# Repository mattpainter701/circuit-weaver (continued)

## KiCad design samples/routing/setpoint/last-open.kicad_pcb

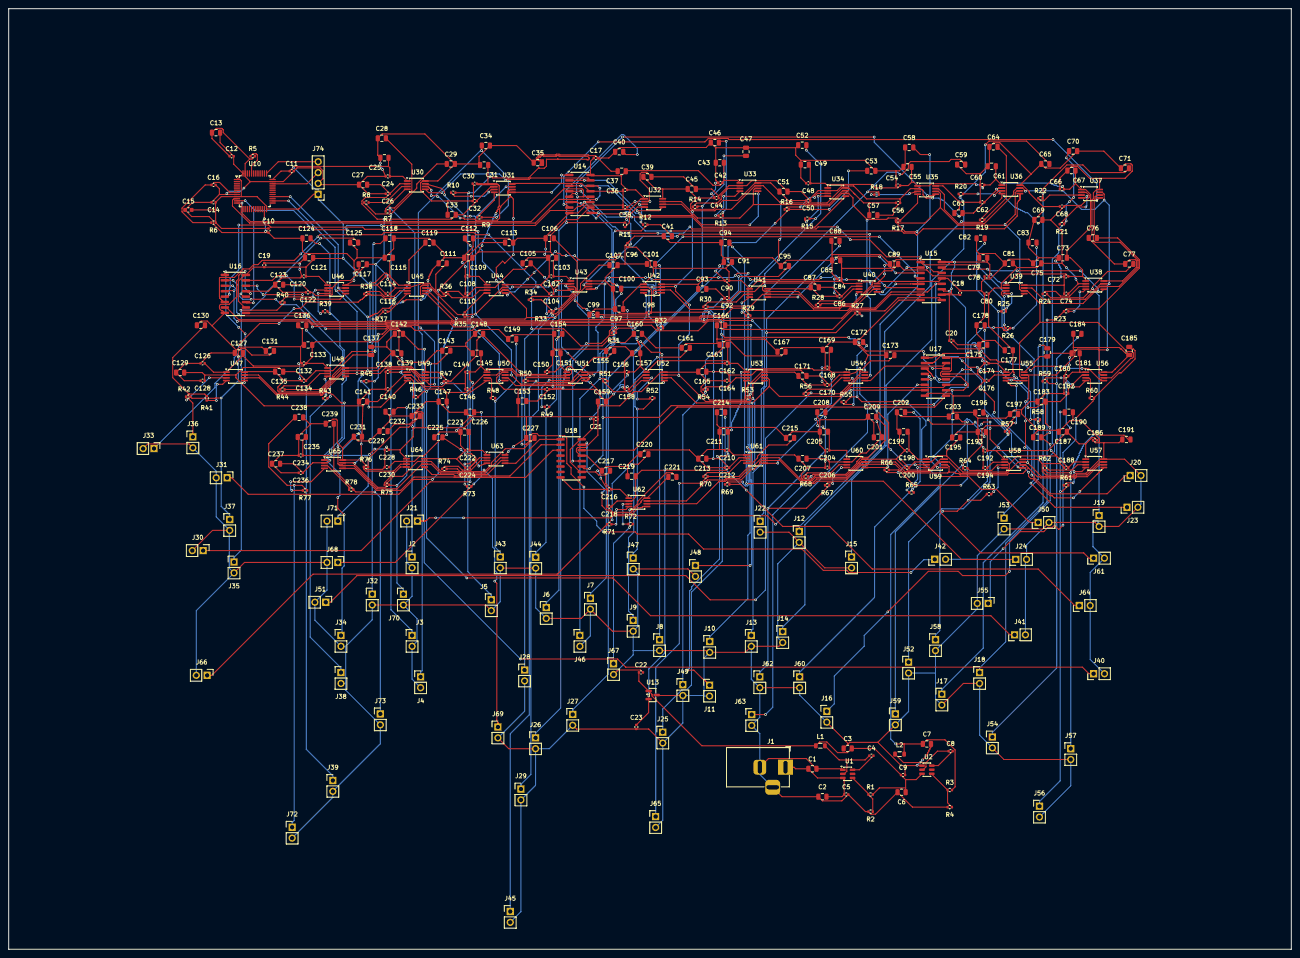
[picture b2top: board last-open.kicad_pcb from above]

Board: 2 copper layers, 300.0 x 220.0 mm, 438 parts (0 on the bottom side), 204 nets.

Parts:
C1, C2, C6, C25, C27, C31, C33, C37, C39, C43, C45, C49, C51, C55, C57, C61, C63, C67, C69, C73, C75, C79, C81, C85, C87, C91, C93, C97, C99, C103, C105, C109, C111, C115, C117, C121, C123, C127, C129, C133, C135, C139, C141, C145, C147, C151, C153, C157, C159, C163, C165, C169, C171, C175, C177, C181, C183, C187, C189, C193, C195, C199, C201, C205, C207, C211, C213, C217, C219, C223, C225, C229, C231, C235, C237: 10uF; C_0805_2012Metric
C3: 6.2uF; C_0805_2012Metric
C4, C5, C8, C9, C10, C11, C12, C16, C17, C18, C19, C20, C21, C22, C23, C24, C26, C30, C32, C36, C38, C42, C44, C48, C50, C54, C56, C60, C62, C66, C68, C72, C74, C78, C80, C84, C86, C90, C92, C96, C98, C102, C104, C108, C110, C114, C116, C120, C122, C126, C128, C132, C134, C138, C140, C144, C146, C150, C152, C156, C158, C162, C164, C168, C170, C174, C176, C180, C182, C186, C188, C192, C194, C198, C200, C204, C206, C210, C212, C216, C218, C222, C224, C228, C230, C234, C236: 100nF; C_0402_1005Metric
C7: 3.3uF; C_0805_2012Metric
C13: 4.7uF; C_0805_2012Metric
C14: 10nF; C_0402_1005Metric
C15: 1uF; C_0603_1608Metric
C28, C29, C34, C35, C40, C41, C46, C47, C52, C53, C58, C59, C64, C65, C70, C71, C76, C77, C82, C83, C88, C89, C94, C95, C100, C101, C106, C107, C112, C113, C118, C119, C124, C125, C130, C131, C136, C137, C142, C143, C148, C149, C154, C155, C160, C161, C166, C167, C172, C173, C178, C179, C184, C185, C190, C191, C196, C197, C202, C203, C208, C209, C214, C215, C220, C221, C226, C227, C232, C233, C238, C239: 1.5uF; C_0805_2012Metric
J1: BARREL_JACK_2.1MM; BarrelJack_Horizontal
J2, J3, J4, J5, J6, J7, J8, J9, J10, J11, J12, J13, J14, J15, J16, J17, J18, J19, J20, J21, J22, J23, J24, J25, J26, J27, J28, J29, J30, J31, J32, J33, J34, J35, J36, J37, J38, J39, J40, J41, J42, J43, J44, J45, J46, J47, J48, J49, J50, J51, J52, J53, J54, J55, J56, J57, J58, J59, J60, J61, J62, J63, J64, J65, J66, J67, J68, J69, J70, J71, J72, J73: PIN_HEADER_2P; PinHeader_1x02_P2.54mm_Vertical
J74: PIN_HEADER_4P; PinHeader_1x04_P2.54mm_Vertical
L1: 8.2uH; L_0805_2012Metric
L2: 6.2uH; L_0805_2012Metric
R1: 1.05M; R_0402_1005Metric
R2: 200k; R_0402_1005Metric
R3: 357k; R_0402_1005Metric
R4: 115k; R_0402_1005Metric
R5, R6: 10k; R_0402_1005Metric
R7, R8, R9, R10, R11, R12, R13, R14, R15, R16, R17, R18, R19, R20, R21, R22, R23, R24, R25, R26, R27, R28, R29, R30, R31, R32, R33, R34, R35, R36, R37, R38, R39, R40, R41, R42, R43, R44, R45, R46, R47, R48, R49, R50, R51, R52, R53, R54, R55, R56, R57, R58, R59, R60, R61, R62, R63, R64, R65, R66, R67, R68, R69, R70, R71, R72, R73, R74, R75, R76, R77, R78: 1k; R_0402_1005Metric
U1, U2: AP62300; SOT-23-6
U10: STM32F103C8T6; LQFP-48_7x7mm_P0.5mm
U13: REF3033; SOT-23
U14, U15, U16, U17, U18: 74HC595D; SOIC-16_3.9x9.9mm_P1.27mm
U30, U31, U32, U33, U34, U35, U36, U37, U38, U39, U40, U41, U42, U43, U44, U45, U46, U47, U48, U49, U50, U51, U52, U53, U54, U55, U56, U57, U58, U59, U60, U61, U62, U63, U64, U65: DAC8552IDGK; MSOP-8_3x3mm_P0.65mm

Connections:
BOOT0: R5.1, U10.44
BST_U1: C4.2, U1.6
BST_U2: C8.2, U2.6
DAC_REF_3V3: C23.1, C26.2, C27.2, C32.2, C33.2, C38.2, C39.2, C44.2, C45.2, C50.2, C51.2, C56.2, C57.2, C62.2, C63.2, C68.2, C69.2, C74.2, C75.2, C80.2, C81.2, C86.2, C87.2, C92.2, C93.2, C98.2, C99.2, C104.2, C105.2, C110.2, C111.2, C116.2, C117.2, C122.2, C123.2, C128.2, C129.2, C134.2, C135.2, C140.2, C141.2, C146.2, C147.2, C152.2, C153.2, C158.2, C159.2, C164.2, C165.2, C170.2, C171.2, C176.2, C177.2, C182.2, C183.2, C188.2, C189.2, C194.2, C195.2, C200.2, C201.2, C206.2, C207.2, C212.2, C213.2, C218.2, C219.2, C224.2, C225.2, C230.2, C231.2, C236.2, C237.2, U13.2, U30.2, U31.2, U32.2, U33.2, U34.2, U35.2, U36.2, U37.2, U38.2, U39.2, U40.2, U41.2, U42.2, U43.2, U44.2, U45.2, U46.2, U47.2, U48.2, U49.2, U50.2, U51.2, U52.2, U53.2, U54.2, U55.2, U56.2, U57.2, U58.2, U59.2, U60.2, U61.2, U62.2, U63.2, U64.2, U65.2
DAC_SYNC_01: U14.15, U30.5
DAC_SYNC_02: U14.1, U31.5
DAC_SYNC_03: U14.2, U32.5
DAC_SYNC_04: U14.3, U33.5
DAC_SYNC_05: U14.4, U34.5
DAC_SYNC_06: U14.5, U35.5
DAC_SYNC_07: U14.6, U36.5
DAC_SYNC_08: U14.7, U37.5
DAC_SYNC_09: U15.15, U38.5
DAC_SYNC_10: U15.1, U39.5
DAC_SYNC_11: U15.2, U40.5
DAC_SYNC_12: U15.3, U41.5
DAC_SYNC_13: U15.4, U42.5
DAC_SYNC_14: U15.5, U43.5
DAC_SYNC_15: U15.6, U44.5
DAC_SYNC_16: U15.7, U45.5
DAC_SYNC_17: U16.15, U46.5
DAC_SYNC_18: U16.1, U47.5
DAC_SYNC_19: U16.2, U48.5
DAC_SYNC_20: U16.3, U49.5
DAC_SYNC_21: U16.4, U50.5
DAC_SYNC_22: U16.5, U51.5
DAC_SYNC_23: U16.6, U52.5
DAC_SYNC_24: U16.7, U53.5
DAC_SYNC_25: U17.15, U54.5
DAC_SYNC_26: U17.1, U55.5
DAC_SYNC_27: U17.2, U56.5
DAC_SYNC_28: U17.3, U57.5
DAC_SYNC_29: U17.4, U58.5
DAC_SYNC_30: U17.5, U59.5
DAC_SYNC_31: U17.6, U60.5
DAC_SYNC_32: U17.7, U61.5
DAC_SYNC_33: U18.15, U62.5
DAC_SYNC_34: U18.1, U63.5
DAC_SYNC_35: U18.2, U64.5
DAC_SYNC_36: U18.3, U65.5
FB_U1: R1.1, R2.2, U1.4
FB_U2: R3.1, R4.2, U2.4
GND: C1.2, C2.1, C3.1, C5.2, C6.1, C7.1, C9.2, C10.1, C11.1, C12.1, C13.1, C14.1, C15.1, C16.2, C17.2, C18.2, C19.2, C20.2, C21.2, C22.2, C23.2, C24.1, C25.1, C26.1, C27.1, C28.1, C29.1, C30.1, C31.1, C32.1, C33.1, C34.1, C35.1, C36.1, C37.1, C38.1, C39.1, C40.1, C41.1, C42.1, C43.1, C44.1, C45.1, C46.1, C47.1, C48.1, C49.1, C50.1, C51.1, C52.1, C53.1, C54.1, C55.1, C56.1, C57.1, C58.1, C59.1, C60.1, C61.1, C62.1, C63.1, C64.1, C65.1, C66.1, C67.1, C68.1, C69.1, C70.1, C71.1, C72.1, C73.1, C74.1, C75.1, C76.1, C77.1, C78.1, C79.1, C80.1, C81.1, C82.1, C83.1, C84.1, C85.1, C86.1, C87.1, C88.1, C89.1, C90.1, C91.1, C92.1, C93.1, C94.1, C95.1, C96.1, C97.1, C98.1, C99.1, C100.1, C101.1, C102.1, C103.1, C104.1, C105.1, C106.1, C107.1, C108.1, C109.1, C110.1, C111.1, C112.1, C113.1, C114.1, C115.1, C116.1, C117.1, C118.1, C119.1, C120.1, C121.1, C122.1, C123.1, C124.1, C125.1, C126.1, C127.1, C128.1, C129.1, C130.1, C131.1, C132.1, C133.1, C134.1, C135.1, C136.1, C137.1, C138.1, C139.1, C140.1, C141.1, C142.1, C143.1, C144.1, C145.1, C146.1, C147.1, C148.1, C149.1, C150.1, C151.1, C152.1, C153.1, C154.1, C155.1, C156.1, C157.1, C158.1, C159.1, C160.1, C161.1, C162.1, C163.1, C164.1, C165.1, C166.1, C167.1, C168.1, C169.1, C170.1, C171.1, C172.1, C173.1, C174.1, C175.1, C176.1, C177.1, C178.1, C179.1, C180.1, C181.1, C182.1, C183.1, C184.1, C185.1, C186.1, C187.1, C188.1, C189.1, C190.1, C191.1, C192.1, C193.1, C194.1, C195.1, C196.1, C197.1, C198.1, C199.1, C200.1, C201.1, C202.1, C203.1, C204.1, C205.1, C206.1, C207.1, C208.1, C209.1, C210.1, C211.1, C212.1, C213.1, C214.1, C215.1, C216.1, C217.1, C218.1, C219.1, C220.1, C221.1, C222.1, C223.1, C224.1, C225.1, C226.1, C227.1, C228.1, C229.1, C230.1, C231.1, C232.1, C233.1, C234.1, C235.1, C236.1, C237.1, C238.1, C239.1, J1.2, J1.3, J2.2, J3.2, J4.2, J5.2, J6.2, J7.2, J8.2, J9.2, J10.2, J11.2, J12.2, J13.2, J14.2, J15.2, J16.2, J17.2, J18.2, J19.2, J20.2, J21.2, J22.2, J23.2, J24.2, J25.2, J26.2, J27.2, J28.2, J29.2, J30.2, J31.2, J32.2, J33.2, J34.2, J35.2, J36.2, J37.2, J38.2, J39.2, J40.2, J41.2, J42.2, J43.2, J44.2, J45.2, J46.2, J47.2, J48.2, J49.2, J50.2, J51.2, J52.2, J53.2, J54.2, J55.2, J56.2, J57.2, J58.2, J59.2, J60.2, J61.2, J62.2, J63.2, J64.2, J65.2, J66.2, J67.2, J68.2, J69.2, J70.2, J71.2, J72.2, J73.2, J74.2, R2.1, R4.1, R5.2, U1.1, U2.1, U10.8, U10.23, U10.35, U10.47, U13.3, U14.8, U14.13, U15.8, U15.13, U16.8, U16.13, U17.8, U17.13, U18.8, U18.13, U30.8, U31.8, U32.8, U33.8, U34.8, U35.8, U36.8, U37.8, U38.8, U39.8, U40.8, U41.8, U42.8, U43.8, U44.8, U45.8, U46.8, U47.8, U48.8, U49.8, U50.8, U51.8, U52.8, U53.8, U54.8, U55.8, U56.8, U57.8, U58.8, U59.8, U60.8, U61.8, U62.8, U63.8, U64.8, U65.8
RESET_N: C16.1, R6.1, U10.7
SETPOINT_01: C28.2, J2.1, R7.2
SETPOINT_02: C29.2, J3.1, R8.2
SETPOINT_03: C34.2, J4.1, R9.2
SETPOINT_04: C35.2, J5.1, R10.2
SETPOINT_05: C40.2, J6.1, R11.2
SETPOINT_06: C41.2, J7.1, R12.2
SETPOINT_07: C46.2, J8.1, R13.2
SETPOINT_08: C47.2, J9.1, R14.2
SETPOINT_09: C52.2, J10.1, R15.2
SETPOINT_10: C53.2, J11.1, R16.2
SETPOINT_11: C58.2, J12.1, R17.2
SETPOINT_12: C59.2, J13.1, R18.2
SETPOINT_13: C64.2, J14.1, R19.2
SETPOINT_14: C65.2, J15.1, R20.2
SETPOINT_15: C70.2, J16.1, R21.2
SETPOINT_16: C71.2, J17.1, R22.2
SETPOINT_17: C76.2, J18.1, R23.2
SETPOINT_18: C77.2, J19.1, R24.2
SETPOINT_19: C82.2, J20.1, R25.2
SETPOINT_20: C83.2, J21.1, R26.2
SETPOINT_21: C88.2, J22.1, R27.2
SETPOINT_22: C89.2, J23.1, R28.2
SETPOINT_23: C94.2, J24.1, R29.2
SETPOINT_24: C95.2, J25.1, R30.2
SETPOINT_25: C100.2, J26.1, R31.2
SETPOINT_26: C101.2, J27.1, R32.2
SETPOINT_27: C106.2, J28.1, R33.2
SETPOINT_28: C107.2, J29.1, R34.2
SETPOINT_29: C112.2, J30.1, R35.2
SETPOINT_30: C113.2, J31.1, R36.2
SETPOINT_31: C118.2, J32.1, R37.2
SETPOINT_32: C119.2, J33.1, R38.2
SETPOINT_33: C124.2, J34.1, R39.2
SETPOINT_34: C125.2, J35.1, R40.2
SETPOINT_35: C130.2, J36.1, R41.2
SETPOINT_36: C131.2, J37.1, R42.2
SETPOINT_37: C136.2, J38.1, R43.2
SETPOINT_38: C137.2, J39.1, R44.2
SETPOINT_39: C142.2, J40.1, R45.2
SETPOINT_40: C143.2, J41.1, R46.2
SETPOINT_41: C148.2, J42.1, R47.2
SETPOINT_42: C149.2, J43.1, R48.2
SETPOINT_43: C154.2, J44.1, R49.2
SETPOINT_44: C155.2, J45.1, R50.2
SETPOINT_45: C160.2, J46.1, R51.2
SETPOINT_46: C161.2, J47.1, R52.2
SETPOINT_47: C166.2, J48.1, R53.2
SETPOINT_48: C167.2, J49.1, R54.2
SETPOINT_49: C172.2, J50.1, R55.2
SETPOINT_50: C173.2, J51.1, R56.2
SETPOINT_51: C178.2, J52.1, R57.2
SETPOINT_52: C179.2, J53.1, R58.2
SETPOINT_53: C184.2, J54.1, R59.2
SETPOINT_54: C185.2, J55.1, R60.2
SETPOINT_55: C190.2, J56.1, R61.2
SETPOINT_56: C191.2, J57.1, R62.2
SETPOINT_57: C196.2, J58.1, R63.2
SETPOINT_58: C197.2, J59.1, R64.2
SETPOINT_59: C202.2, J60.1, R65.2
SETPOINT_60: C203.2, J61.1, R66.2
SETPOINT_61: C208.2, J62.1, R67.2
SETPOINT_62: C209.2, J63.1, R68.2
SETPOINT_63: C214.2, J64.1, R69.2
SETPOINT_64: C215.2, J65.1, R70.2
SETPOINT_65: C220.2, J66.1, R71.2
SETPOINT_66: C221.2, J67.1, R72.2
SETPOINT_67: C226.2, J68.1, R73.2
SETPOINT_68: C227.2, J69.1, R74.2
SETPOINT_69: C232.2, J70.1, R75.2
SETPOINT_70: C233.2, J71.1, R76.2
SETPOINT_71: C238.2, J72.1, R77.2
SETPOINT_72: C239.2, J73.1, R78.2
SHIFT_CLOCK: U10.11, U14.11, U15.11, U16.11, U17.11, U18.11
SHIFT_DATA: U10.10, U14.14
SHIFT_LATCH: U10.12, U14.12, U15.12, U16.12, U17.12, U18.12
SHIFT_QH_1: U14.9, U15.14
SHIFT_QH_2: U15.9, U16.14
SHIFT_QH_3: U16.9, U17.14
SHIFT_QH_4: U17.9, U18.14
SPI_MOSI: U10.28, U30.7, U31.7, U32.7, U33.7, U34.7, U35.7, U36.7, U37.7, U38.7, U39.7, U40.7, U41.7, U42.7, U43.7, U44.7, U45.7, U46.7, U47.7, U48.7, U49.7, U50.7, U51.7, U52.7, U53.7, U54.7, U55.7, U56.7, U57.7, U58.7, U59.7, U60.7, U61.7, U62.7, U63.7, U64.7, U65.7
SPI_SCK: U10.26, U30.6, U31.6, U32.6, U33.6, U34.6, U35.6, U36.6, U37.6, U38.6, U39.6, U40.6, U41.6, U42.6, U43.6, U44.6, U45.6, U46.6, U47.6, U48.6, U49.6, U50.6, U51.6, U52.6, U53.6, U54.6, U55.6, U56.6, U57.6, U58.6, U59.6, U60.6, U61.6, U62.6, U63.6, U64.6, U65.6
SWCLK: J74.4, U10.37
SWDIO: J74.3, U10.34
SW_U1: C4.1, L1.1, U1.2
SW_U2: C8.1, L2.1, U2.2
VDD_3P3: C7.2, C10.2, C11.2, C12.2, C13.2, C14.2, C15.2, C17.1, C18.1, C19.1, C20.1, C21.1, C24.2, C25.2, C30.2, C31.2, C36.2, C37.2, C42.2, C43.2, C48.2, C49.2, C54.2, C55.2, C60.2, C61.2, C66.2, C67.2, C72.2, C73.2, C78.2, C79.2, C84.2, C85.2, C90.2, C91.2, C96.2, C97.2, C102.2, C103.2, C108.2, C109.2, C114.2, C115.2, C120.2, C121.2, C126.2, C127.2, C132.2, C133.2, C138.2, C139.2, C144.2, C145.2, C150.2, C151.2, C156.2, C157.2, C162.2, C163.2, C168.2, C169.2, C174.2, C175.2, C180.2, C181.2, C186.2, C187.2, C192.2, C193.2, C198.2, C199.2, C204.2, C205.2, C210.2, C211.2, C216.2, C217.2, C222.2, C223.2, C228.2, C229.2, C234.2, C235.2, J74.1, L2.2, R3.2, R6.2, U10.1, U10.9, U10.24, U10.36, U10.48, U14.10, U14.16, U15.10, U15.16, U16.10, U16.16, U17.10, U17.16, U18.10, U18.16, U30.1, U31.1, U32.1, U33.1, U34.1, U35.1, U36.1, U37.1, U38.1, U39.1, U40.1, U41.1, U42.1, U43.1, U44.1, U45.1, U46.1, U47.1, U48.1, U49.1, U50.1, U51.1, U52.1, U53.1, U54.1, U55.1, U56.1, U57.1, U58.1, U59.1, U60.1, U61.1, U62.1, U63.1, U64.1, U65.1
VDD_5V: C3.2, C6.2, C9.1, C22.1, L1.2, R1.2, U2.3, U13.1
VIN_12V: C1.1, C2.2, C5.1, J1.1, U1.3
VOUTA_RAW_U30: R7.1, U30.4
VOUTA_RAW_U31: R9.1, U31.4
VOUTA_RAW_U32: R11.1, U32.4
VOUTA_RAW_U33: R13.1, U33.4
VOUTA_RAW_U34: R15.1, U34.4
VOUTA_RAW_U35: R17.1, U35.4
VOUTA_RAW_U36: R19.1, U36.4
VOUTA_RAW_U37: R21.1, U37.4
VOUTA_RAW_U38: R23.1, U38.4
VOUTA_RAW_U39: R25.1, U39.4
VOUTA_RAW_U40: R27.1, U40.4
VOUTA_RAW_U41: R29.1, U41.4
VOUTA_RAW_U42: R31.1, U42.4
VOUTA_RAW_U43: R33.1, U43.4
VOUTA_RAW_U44: R35.1, U44.4
VOUTA_RAW_U45: R37.1, U45.4
VOUTA_RAW_U46: R39.1, U46.4
VOUTA_RAW_U47: R41.1, U47.4
VOUTA_RAW_U48: R43.1, U48.4
VOUTA_RAW_U49: R45.1, U49.4
VOUTA_RAW_U50: R47.1, U50.4
VOUTA_RAW_U51: R49.1, U51.4
VOUTA_RAW_U52: R51.1, U52.4
VOUTA_RAW_U53: R53.1, U53.4
VOUTA_RAW_U54: R55.1, U54.4
VOUTA_RAW_U55: R57.1, U55.4
VOUTA_RAW_U56: R59.1, U56.4
VOUTA_RAW_U57: R61.1, U57.4
VOUTA_RAW_U58: R63.1, U58.4
VOUTA_RAW_U59: R65.1, U59.4
VOUTA_RAW_U60: R67.1, U60.4
VOUTA_RAW_U61: R69.1, U61.4
VOUTA_RAW_U62: R71.1, U62.4
VOUTA_RAW_U63: R73.1, U63.4
VOUTA_RAW_U64: R75.1, U64.4
VOUTA_RAW_U65: R77.1, U65.4
VOUTB_RAW_U30: R8.1, U30.3
VOUTB_RAW_U31: R10.1, U31.3
VOUTB_RAW_U32: R12.1, U32.3
VOUTB_RAW_U33: R14.1, U33.3
VOUTB_RAW_U34: R16.1, U34.3
VOUTB_RAW_U35: R18.1, U35.3
VOUTB_RAW_U36: R20.1, U36.3
VOUTB_RAW_U37: R22.1, U37.3
VOUTB_RAW_U38: R24.1, U38.3
VOUTB_RAW_U39: R26.1, U39.3
VOUTB_RAW_U40: R28.1, U40.3
VOUTB_RAW_U41: R30.1, U41.3
VOUTB_RAW_U42: R32.1, U42.3
VOUTB_RAW_U43: R34.1, U43.3
VOUTB_RAW_U44: R36.1, U44.3
VOUTB_RAW_U45: R38.1, U45.3
VOUTB_RAW_U46: R40.1, U46.3
VOUTB_RAW_U47: R42.1, U47.3
VOUTB_RAW_U48: R44.1, U48.3
VOUTB_RAW_U49: R46.1, U49.3
VOUTB_RAW_U50: R48.1, U50.3
VOUTB_RAW_U51: R50.1, U51.3
VOUTB_RAW_U52: R52.1, U52.3
VOUTB_RAW_U53: R54.1, U53.3
VOUTB_RAW_U54: R56.1, U54.3
VOUTB_RAW_U55: R58.1, U55.3
VOUTB_RAW_U56: R60.1, U56.3
VOUTB_RAW_U57: R62.1, U57.3
VOUTB_RAW_U58: R64.1, U58.3
VOUTB_RAW_U59: R66.1, U59.3
VOUTB_RAW_U60: R68.1, U60.3
VOUTB_RAW_U61: R70.1, U61.3
VOUTB_RAW_U62: R72.1, U62.3
VOUTB_RAW_U63: R74.1, U63.3
VOUTB_RAW_U64: R76.1, U64.3
VOUTB_RAW_U65: R78.1, U65.3

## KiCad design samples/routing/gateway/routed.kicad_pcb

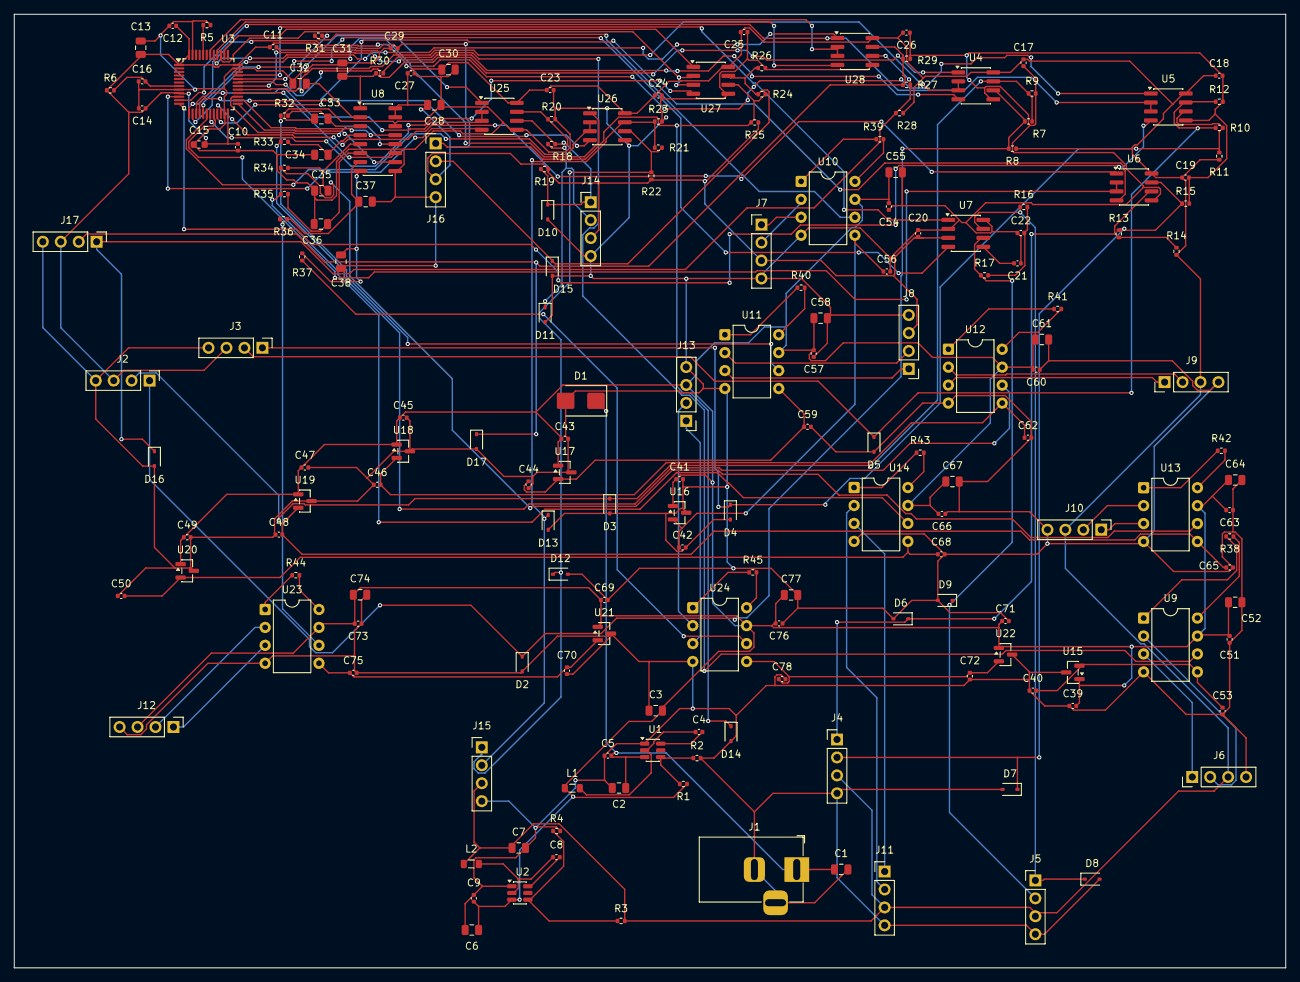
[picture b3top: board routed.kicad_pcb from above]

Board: 2 copper layers, 180.0 x 135.0 mm, 187 parts (0 on the bottom side), 113 nets.

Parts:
C1, C2, C6, C28, C30, C52, C55, C58, C61, C64, C67, C74, C77: 10uF; C_0805_2012Metric
C3: 6.2uF; C_0805_2012Metric
C4, C5, C8, C9, C10, C11, C12, C16, C17, C18, C19, C20, C21, C23, C24, C25, C26, C27, C29, C39, C40, C41, C42, C43, C44, C45, C46, C47, C48, C49, C50, C51, C53, C54, C56, C57, C59, C60, C62, C63, C65, C66, C68, C69, C70, C71, C72, C73, C75, C76, C78: 100nF; C_0402_1005Metric
C7: 3.3uF; C_0805_2012Metric
C13: 4.7uF; C_0805_2012Metric
C14: 10nF; C_0402_1005Metric
C15: 1uF; C_0603_1608Metric
C22: 4.7nF; C_0402_1005Metric
C31, C32, C33, C34, C35, C36, C37, C38: 680nF; C_0805_2012Metric
D1: SMBJ12A; D_SMB
D2, D3, D4, D5, D6, D7, D8, D9, D10, D11, D12, D13, D14, D15, D16, D17: PESD5V0S1BA; D_SOD-323
J1: BARREL_JACK_2.1MM; BarrelJack_Horizontal
J2, J3, J4, J5, J6, J7, J8, J9, J10, J11, J12, J13, J14, J15, J16, J17: PIN_HEADER_4P; PinHeader_1x04_P2.54mm_Vertical
L1: 8.2uH; L_0805_2012Metric
L2: 6.2uH; L_0805_2012Metric
R1: 1.05M; R_0402_1005Metric
R2: 200k; R_0402_1005Metric
R3: 357k; R_0402_1005Metric
R4: 115k; R_0402_1005Metric
R5, R6: 10k; R_0402_1005Metric
R7, R10, R13, R18, R21, R24, R27: 120R; R_0402_1005Metric
R8, R9, R11, R12, R14, R15, R19, R20, R22, R23, R25, R26, R28, R29: 390R; R_0402_1005Metric
R16, R17: 60.4R; R_0402_1005Metric
R30, R31, R32, R33, R34, R35, R36, R37: 1k; R_0402_1005Metric
R38, R39, R40, R41, R42, R43, R44, R45: 12.4k; R_0402_1005Metric
U1, U2: AP62300; SOT-23-6
U3: STM32F103C8T6; LQFP-48_7x7mm_P0.5mm
U4, U5, U6, U25, U26, U27, U28: SP3485EN-L/TR; SOIC-8_3.9x4.9mm_P1.27mm
U7: SN65HVD230; SOIC-8_3.9x4.9mm_P1.27mm
U8: MCP3208-CI/SL; SOIC-16_3.9x9.9mm_P1.27mm
U9, U10, U11, U12, U13, U14, U23, U24: INA128PA; DIP-8_W7.62mm
U15, U16, U17, U18, U19, U20, U21, U22: REF3030; SOT-23

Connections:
BOOT0: R5.1, U3.44
BST_U1: C4.2, U1.6
BST_U2: C8.2, U2.6
CAN_RXD: U3.32, U7.4
CAN_TERM_MID_U7: C22.2, R16.2, R17.1
CAN_TXD: U3.33, U7.1
CAN_VREF_U7: C21.1, U7.5
CH0_U8: R30.1, U9.6
CH1_U8: R31.1, U10.6
CH2_U8: R32.1, U11.6
CH3_U8: R33.1, U12.6
CH4_U8: R34.1, U13.6
CH5_U8: R35.1, U14.6
CH6_U8: R36.1, U23.6
CH7_U8: R37.1, U24.6
FB_U1: R1.1, R2.2, U1.4
FB_U2: R3.1, R4.2, U2.4
FIELD_AI0_N: J6.2, U9.2
FIELD_AI0_P: J6.1, U9.3
FIELD_AI1_N: J7.2, U10.2
FIELD_AI1_P: J7.1, U10.3
FIELD_AI2_N: J8.2, U11.2
FIELD_AI2_P: J8.1, U11.3
FIELD_AI3_N: J9.2, U12.2
FIELD_AI3_P: J9.1, U12.3
FIELD_AI4_N: J10.2, U13.2
FIELD_AI4_P: J10.1, U13.3
FIELD_AI5_N: J11.2, U14.2
FIELD_AI5_P: J11.1, U14.3
FIELD_AI6_N: J12.2, U23.2
FIELD_AI6_P: J12.1, U23.3
FIELD_AI7_N: J13.2, U24.2
FIELD_AI7_P: J13.1, U24.3
FIELD_A_DE: U3.29, U4.2, U4.3
FIELD_A_RS485_A_U4: D2.1, J2.1, R7.1, R8.1, U4.6
FIELD_A_RS485_B_U4: D3.1, J2.2, R7.2, R9.1, U4.7
FIELD_A_RX: U3.31, U4.1
FIELD_A_TX: U3.30, U4.4
FIELD_B_DE: U3.11, U5.2, U5.3
FIELD_B_RS485_A_U5: D4.1, J3.1, R10.1, R11.1, U5.6
FIELD_B_RS485_B_U5: D5.1, J3.2, R10.2, R12.1, U5.7
FIELD_B_RX: U3.13, U5.1
FIELD_B_TX: U3.12, U5.4
FIELD_CAN_H_U7: D8.1, J5.1, R16.1, U7.7
FIELD_CAN_L_U7: D9.1, J5.2, R17.2, U7.6
FIELD_C_DE: U3.20, U6.2, U6.3
FIELD_C_RS485_A_U6: D6.1, J4.1, R13.1, R14.1, U6.6
FIELD_C_RS485_B_U6: D7.1, J4.2, R13.2, R15.1, U6.7
FIELD_C_RX: U3.22, U6.1
FIELD_C_TX: U3.21, U6.4
FIELD_D_DE: U3.15, U25.2, U25.3
FIELD_D_RS485_A_U25: D10.1, J14.1, R18.1, R19.1, U25.6
FIELD_D_RS485_B_U25: D11.1, J14.2, R18.2, R20.1, U25.7
FIELD_D_RX: U3.14, U25.1
FIELD_D_TX: U3.10, U25.4
FIELD_E_DE: U3.18, U26.2, U26.3
FIELD_E_RS485_A_U26: D12.1, J15.1, R21.1, R22.1, U26.6
FIELD_E_RS485_B_U26: D13.1, J15.2, R21.2, R23.1, U26.7
FIELD_E_RX: U3.17, U26.1
FIELD_E_TX: U3.16, U26.4
FIELD_F_DE: U3.39, U27.2, U27.3
FIELD_F_RS485_A_U27: D14.1, J16.1, R24.1, R25.1, U27.6
FIELD_F_RS485_B_U27: D15.1, J16.2, R24.2, R26.1, U27.7
FIELD_F_RX: U3.38, U27.1
FIELD_F_TX: U3.19, U27.4
FIELD_G_DE: U3.42, U28.2, U28.3
FIELD_G_RS485_A_U28: D16.1, J17.1, R27.1, R28.1, U28.6
FIELD_G_RS485_B_U28: D17.1, J17.2, R27.2, R29.1, U28.7
FIELD_G_RX: U3.41, U28.1
FIELD_G_TX: U3.40, U28.4
FILT_CH0_U8: C31.1, R30.2, U8.1
FILT_CH1_U8: C32.1, R31.2, U8.2
FILT_CH2_U8: C33.1, R32.2, U8.3
FILT_CH3_U8: C34.1, R33.2, U8.4
FILT_CH4_U8: C35.1, R34.2, U8.5
FILT_CH5_U8: C36.1, R35.2, U8.6
FILT_CH6_U8: C37.1, R36.2, U8.7
FILT_CH7_U8: C38.1, R37.2, U8.8
GND: C1.2, C2.1, C3.1, C5.2, C6.1, C7.1, C9.2, C10.1, C11.1, C12.1, C13.1, C14.1, C15.1, C16.2, C17.1, C18.1, C19.1, C20.1, C21.2, C22.1, C23.1, C24.1, C25.1, C26.1, C27.1, C28.1, C29.1, C30.1, C31.2, C32.2, C33.2, C34.2, C35.2, C36.2, C37.2, C38.2, C39.2, C40.2, C41.2, C42.2, C43.2, C44.2, C45.2, C46.2, C47.2, C48.2, C49.2, C50.2, C51.1, C52.1, C53.2, C54.1, C55.1, C56.2, C57.1, C58.1, C59.2, C60.1, C61.1, C62.2, C63.1, C64.1, C65.2, C66.1, C67.1, C68.2, C69.2, C70.2, C71.2, C72.2, C73.1, C74.1, C75.2, C76.1, C77.1, C78.2, D1.2, D2.2, D3.2, D4.2, D5.2, D6.2, D7.2, D8.2, D9.2, D10.2, D11.2, D12.2, D13.2, D14.2, D15.2, D16.2, D17.2, J1.2, J1.3, J2.4, J3.4, J4.4, J5.4, J6.4, J7.4, J8.4, J9.4, J10.4, J11.4, J12.4, J13.4, J14.4, J15.4, J16.4, J17.4, R2.1, R4.1, R5.2, R9.2, R12.2, R15.2, R20.2, R23.2, R26.2, R29.2, U1.1, U2.1, U3.8, U3.23, U3.35, U3.47, U4.5, U5.5, U6.5, U7.2, U7.8, U8.9, U8.14, U9.4, U10.4, U11.4, U12.4, U13.4, U14.4, U15.3, U16.3, U17.3, U18.3, U19.3, U20.3, U21.3, U22.3, U23.4, U24.4, U25.5, U26.5, U27.5, U28.5
REF_U9: C40.1, C53.1, U9.5, U15.2
REF_U10: C42.1, C56.1, U10.5, U16.2
REF_U11: C44.1, C59.1, U11.5, U17.2
REF_U12: C46.1, C62.1, U12.5, U18.2
REF_U13: C48.1, C65.1, U13.5, U19.2
REF_U14: C50.1, C68.1, U14.5, U20.2
REF_U23: C70.1, C75.1, U21.2, U23.5
REF_U24: C72.1, C78.1, U22.2, U24.5
RESET_N: C16.1, R6.1, U3.7
RG_N_U9: R38.2, U9.1
RG_N_U10: R39.2, U10.1
RG_N_U11: R40.2, U11.1
RG_N_U12: R41.2, U12.1
RG_N_U13: R42.2, U13.1
RG_N_U14: R43.2, U14.1
RG_N_U23: R44.2, U23.1
RG_N_U24: R45.2, U24.1
RG_P_U9: R38.1, U9.8
RG_P_U10: R39.1, U10.8
RG_P_U11: R40.1, U11.8
RG_P_U12: R41.1, U12.8
RG_P_U13: R42.1, U13.8
RG_P_U14: R43.1, U14.8
RG_P_U23: R44.1, U23.8
RG_P_U24: R45.1, U24.8
SPI_CS_N: U3.25, U8.10
SPI_MISO: U3.27, U8.12
SPI_MOSI: U3.28, U8.11
SPI_SCK: U3.26, U8.13
SW_U1: C4.1, L1.1, U1.2
SW_U2: C8.1, L2.1, U2.2
VDD_3P3: C7.2, C10.2, C11.2, C12.2, C13.2, C14.2, C15.2, C17.2, C18.2, C19.2, C20.2, C23.2, C24.2, C25.2, C26.2, C27.2, C28.2, C29.2, C30.2, J2.3, J3.3, J4.3, J5.3, J6.3, J7.3, J8.3, J9.3, J10.3, J11.3, J14.3, J15.3, J16.3, J17.3, L2.2, R3.2, R6.2, R8.2, R11.2, R14.2, R19.2, R22.2, R25.2, R28.2, U3.1, U3.9, U3.24, U3.36, U3.48, U4.8, U5.8, U6.8, U7.3, U8.15, U8.16, U25.8, U26.8, U27.8, U28.8
VDD_5V: C3.2, C6.2, C9.1, C39.1, C41.1, C43.1, C45.1, C47.1, C49.1, C51.2, C52.2, C54.2, C55.2, C57.2, C58.2, C60.2, C61.2, C63.2, C64.2, C66.2, C67.2, C69.1, C71.1, C73.2, C74.2, C76.2, C77.2, J12.3, J13.3, L1.2, R1.2, U2.3, U9.7, U10.7, U11.7, U12.7, U13.7, U14.7, U15.1, U16.1, U17.1, U18.1, U19.1, U20.1, U21.1, U22.1, U23.7, U24.7
VIN_12V: C1.1, C2.2, C5.1, D1.1, J1.1, U1.3
